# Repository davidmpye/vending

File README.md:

This repository contains my work to reverse engineer and remanufacture vending machine parts to make it easier to keep old machines running!

tray_pcb - 	National Vendors / Crane / Polyvend part number 1596014.  This is referred to as "Tray PCB" and is a drop in replacement for the original board, using THT parts.

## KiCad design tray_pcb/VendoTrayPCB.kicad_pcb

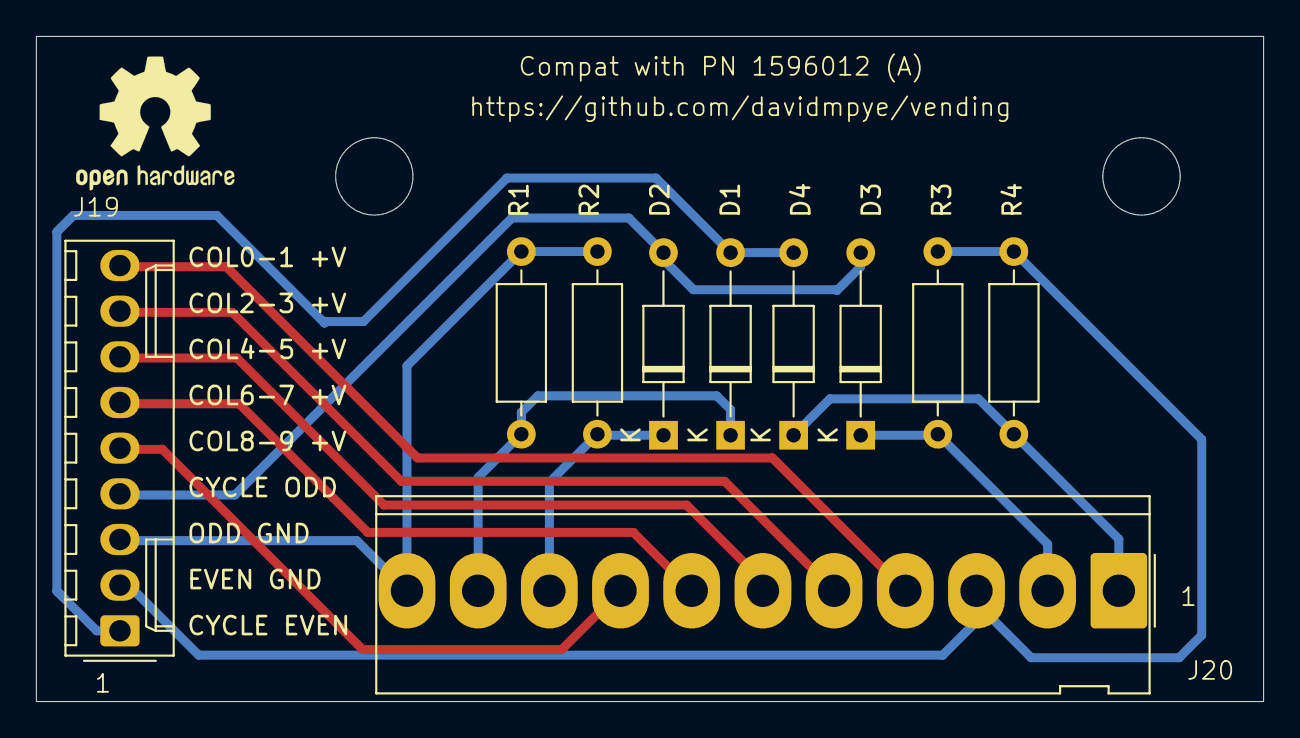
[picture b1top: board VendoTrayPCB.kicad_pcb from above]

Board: 2 copper layers, 68.3 x 37.0 mm, 10 parts (0 on the bottom side), 13 nets.

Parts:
D1, D2, D3, D4: 1N4148; D_DO-35_SOD27_P10.16mm_Horizontal
J1: Bus_conn; Molex_KK-254_AE-6410-09A_1x09_P2.54mm_Vertical
J2: Tray_Conn; Molex_KK-396_5273-11A_1x11_P3.96mm_Vertical
R1, R2, R3, R4: R; R_Axial_DIN0207_L6.3mm_D2.5mm_P10.16mm_Horizontal

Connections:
unnamed: D1.2 (A), D4.2 (A), J1.1
unnamed: D1.1 (K), J2.10, R1.2
unnamed: D2.2 (A), D3.2 (A), J1.4
unnamed: D2.1 (K), J2.9, R2.2
unnamed: D3.1 (K), J2.2, R3.2
unnamed: D4.1 (K), J2.1, R4.2
unnamed: J1.2, J2.3, R3.1, R4.1
unnamed: J1.3, J2.11, R1.1, R2.1
unnamed: J1.5, J2.8
unnamed: J1.6, J2.7
unnamed: J1.7, J2.6
unnamed: J1.8, J2.5
unnamed: J1.9, J2.4

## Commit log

2024-04-20 Initial import of tray pcb
